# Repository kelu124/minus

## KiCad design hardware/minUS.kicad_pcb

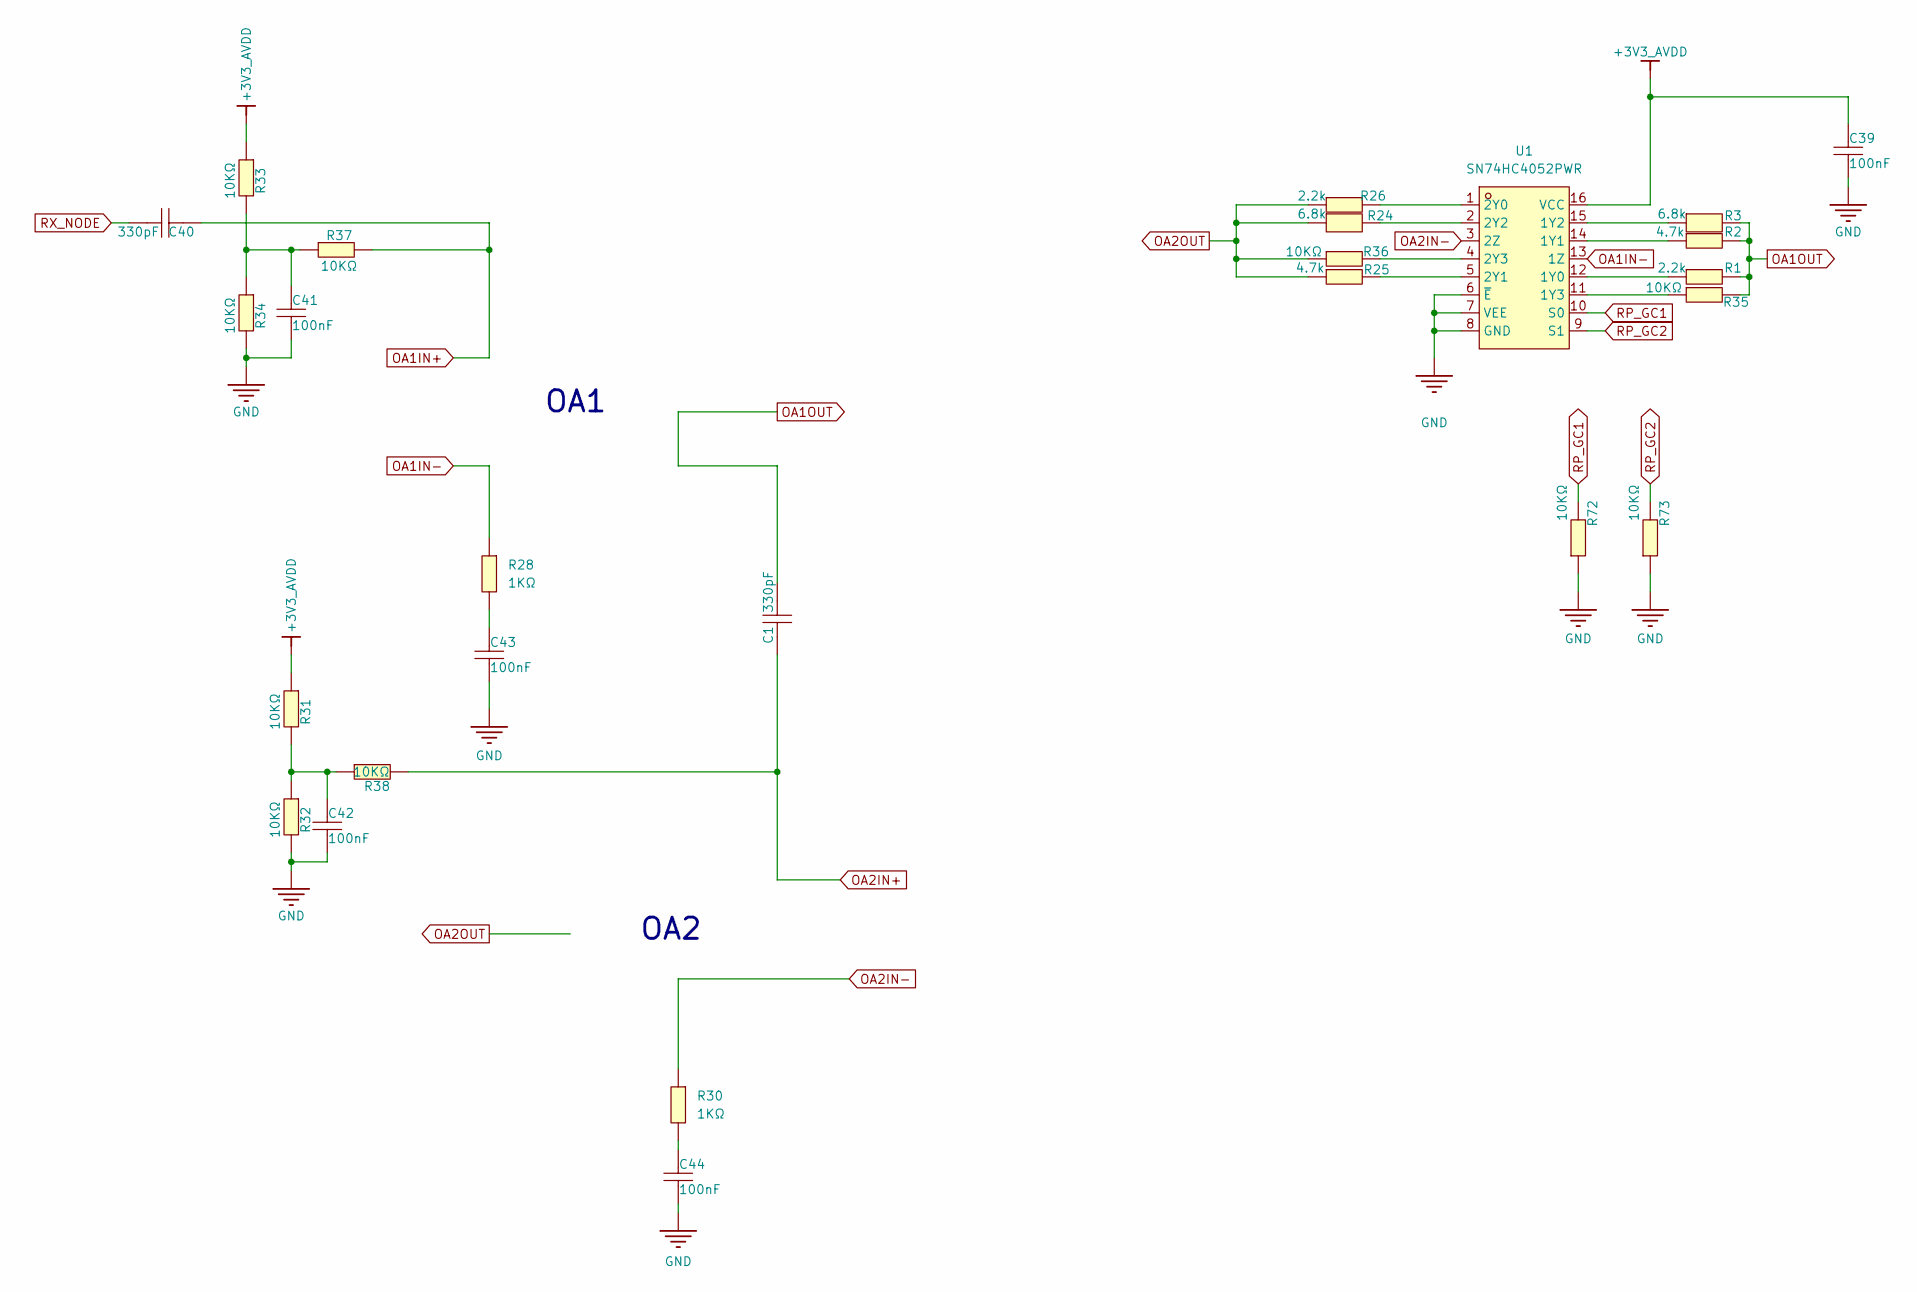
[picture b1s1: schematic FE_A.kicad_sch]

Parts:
C1, C40: CSA0402C0G331J500GT; C0402; MPN CSA0402C0G331J500GT; LCSC Part C48642894
C39, C41, C42, C43, C44: 100nF; C0402; MPN CC0402KRX7R9BB104; LCSC Part C152814
R1, R26: RC0402FR-072K2L; R0402; MPN RC0402FR-072K2L; LCSC Part C114762
R2, R25: RC0402FR-074K7L; R0402; MPN RC0402FR-074K7L; LCSC Part C105871
R3, R24: FRC0402F6801TS; R0402; MPN FRC0402F6801TS; LCSC Part C2906876
R28, R30: 1KΩ; R0402; MPN 0402WGF1001TCE; LCSC Part C11702
R31, R32, R33, R34, R35, R36, R37, R38, R72, R73: 10KΩ; R0402; MPN 0402WGF1002TCE; LCSC Part C25744
U1: SN74HC4052PWR; TSSOP-16_L5.0-W4.3-P0.65-LS6.4-BL; MPN SN74HC4052PWR(LX); LCSC Part C22449643

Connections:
+3V3_AVDD: C39.2, R31.1, R33.1, U1.16 (VCC); also elsewhere on the board
GND: C39.1, C41.1, C42.1, C43.1, C44.1, R32.2, R34.2, R72.1, R73.1, U1.6 (~E), U1.7 (VEE), U1.8 (GND); also elsewhere on the board
unnamed: C41.2, R33.2, R34.1, R37.1
unnamed: C42.2, R31.2, R32.1, R38.1
unnamed: C43.2, R28.2
unnamed: C44.2, R30.2
unnamed: R1.1, U1.12 (1Y0)
unnamed: R2.1, U1.14 (1Y1)
unnamed: R3.1, U1.15 (1Y2)
unnamed: R35.1, U1.11 (1Y3)
unnamed: R26.2, U1.1 (2Y0)
unnamed: R25.2, U1.5 (2Y1)
unnamed: R24.2, U1.2 (2Y2)
unnamed: R36.2, U1.4 (2Y3)
OA1IN+: C40.1, R37.2; also elsewhere on the board
OA1IN-: R28.1, U1.13 (1Z); also elsewhere on the board
OA1OUT: C1.2, R1.2, R2.2, R3.2, R35.2; also elsewhere on the board
OA2IN+: C1.1, R38.2; also elsewhere on the board
OA2IN-: R30.1, U1.3 (2Z); also elsewhere on the board
OA2OUT: R24.1, R25.1, R26.1, R36.1; also elsewhere on the board
RP_GC1: R72.2, U1.10 (S0); also elsewhere on the board
RP_GC2: R73.2, U1.9 (S1); also elsewhere on the board
RX_NODE: C40.2; also elsewhere on the board

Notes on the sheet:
OA1
OA2

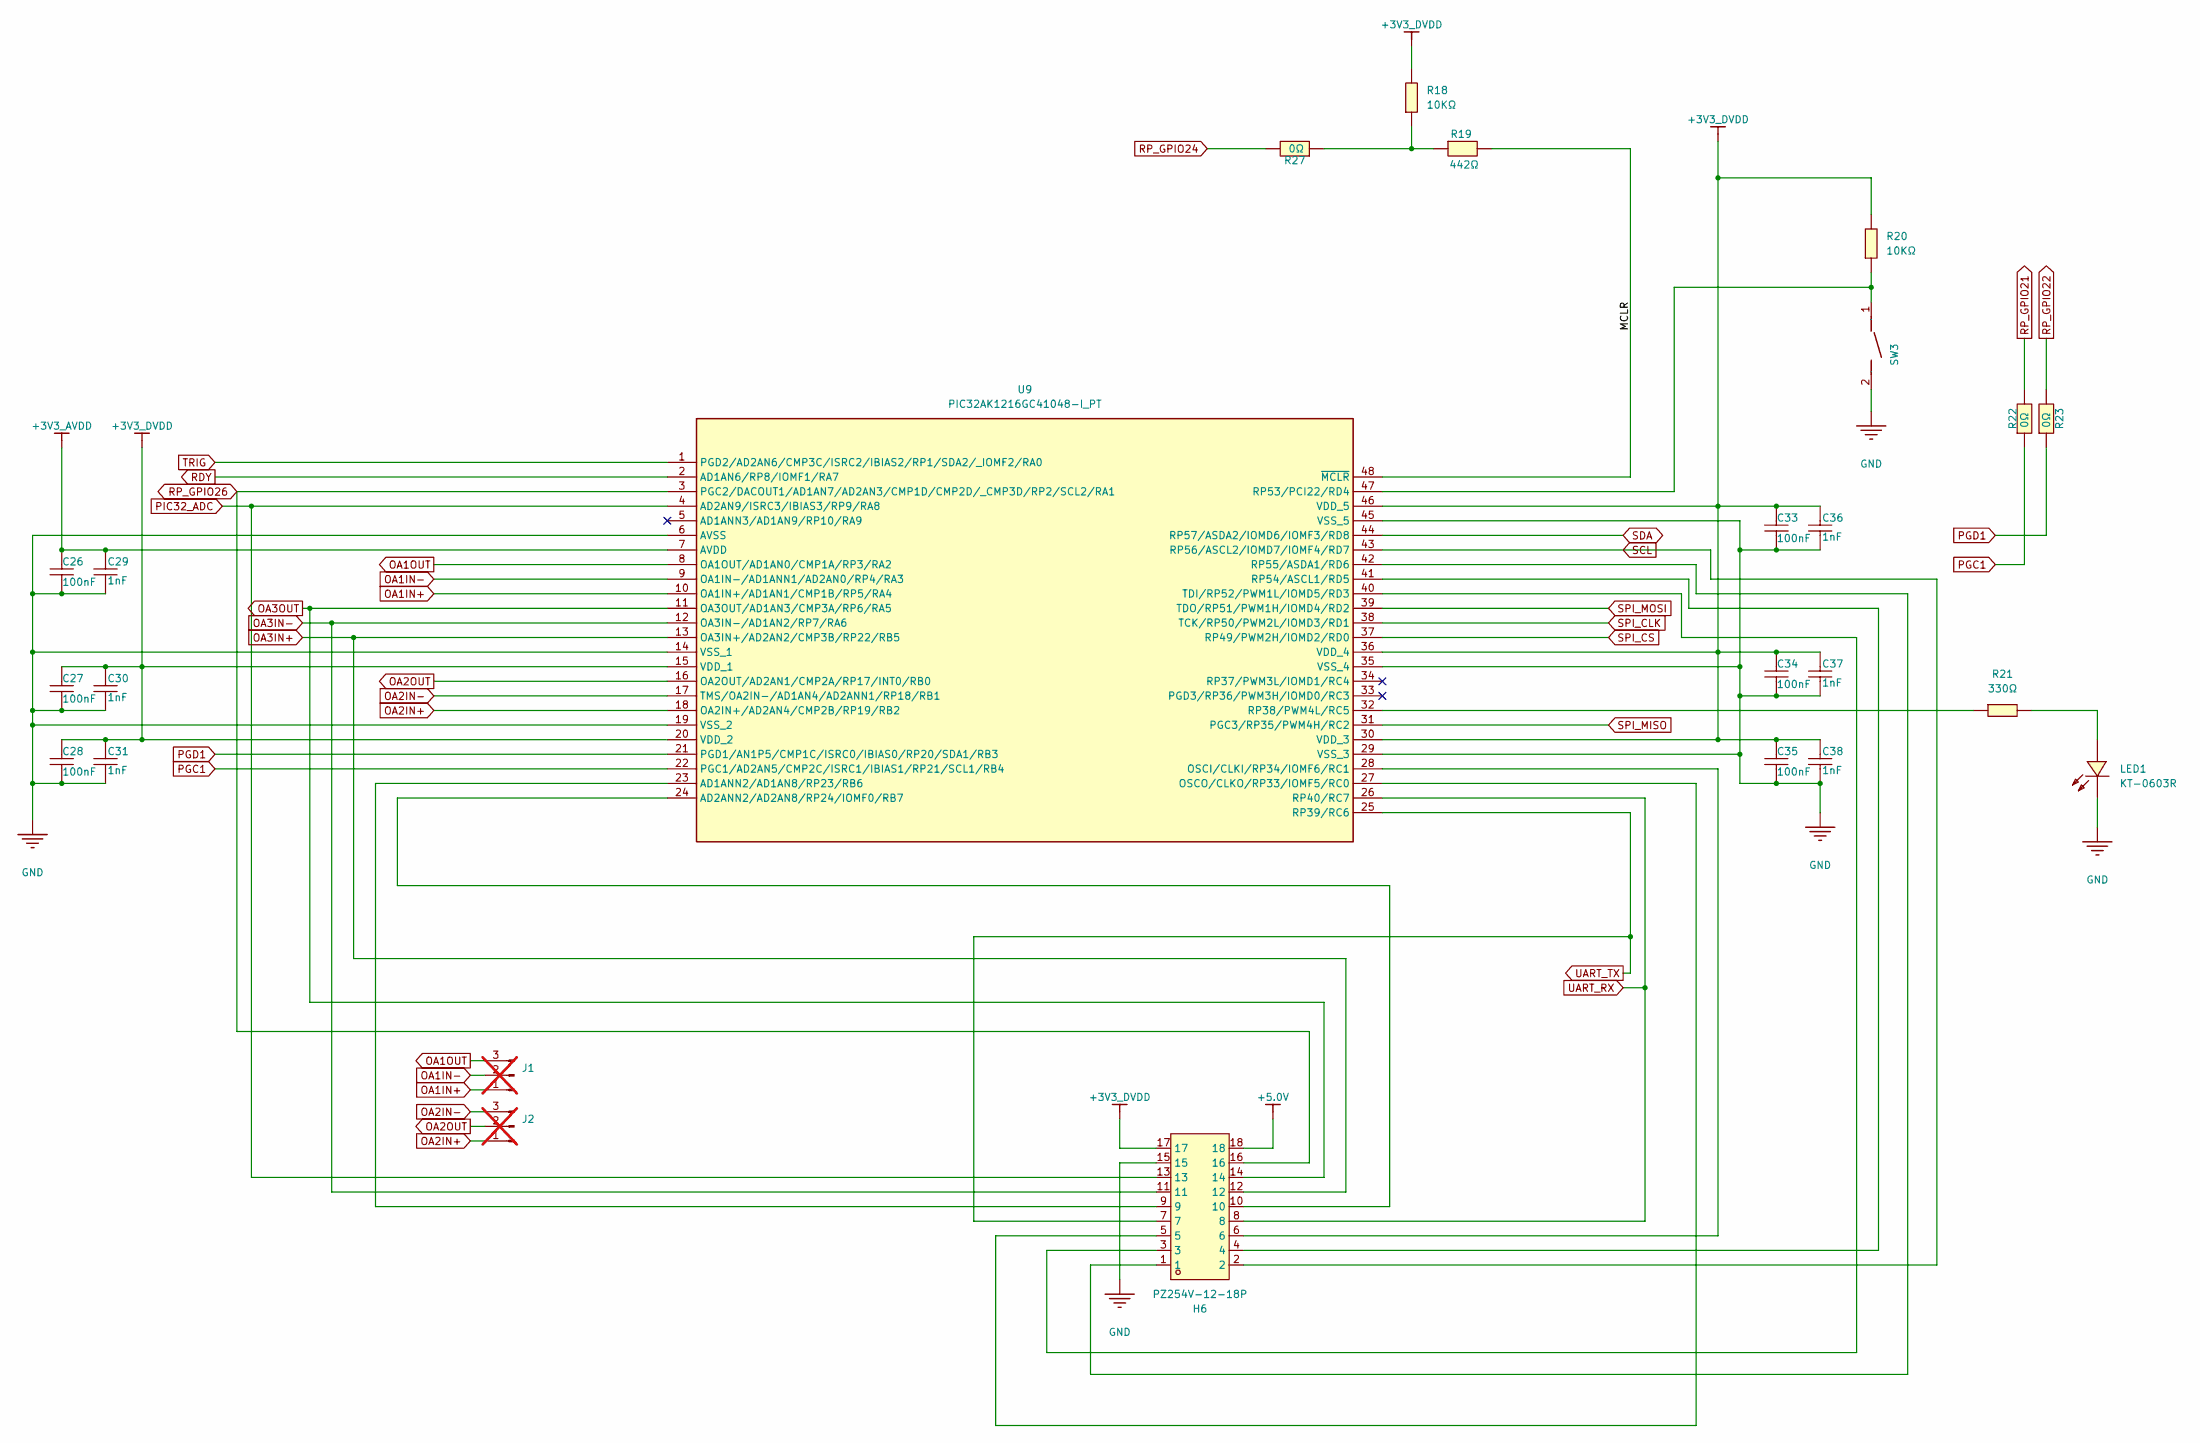
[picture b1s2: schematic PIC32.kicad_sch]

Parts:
C26, C27, C28, C33, C34, C35: 100nF; C0402; MPN CC0402KRX7R9BB104; LCSC Part C152814
C29, C30, C31, C36, C37, C38: 1nF; C0402; MPN CL05B102KB5NNNC; LCSC Part C14442
H6: PZ254V-12-18P; HDR-TH_18P-P2.54-V-M-R2-C9-S2.54; MPN PZ254V-12-18P; LCSC Part C492426
J1, J2: Conn_01x03_Pin; PinSocket_1x03_P2.54mm_Vertical; LCSC Part C49257; not fitted
LED1: KT-0603R; LED-SMD_L1.6-W0.8-R-RD; MPN KT-0603R; LCSC Part C2286
R18, R20: 10KΩ; R0402; MPN 0402WGF1002TCE; LCSC Part C25744
R19: 442Ω; R0402; MPN RC-02K4420FT; LCSC Part C453691
R21: 330Ω; R0402; MPN RC0402FR-07330RL; LCSC Part C105875
R22, R23, R27: 0Ω; R0402; MPN RCS04020000Z0ED; LCSC Part C844673
SW3: TS-1088-AR02016; SW-SMD_L3.9-W3.0-P4.45; Manufacturer Part TS-1088-AR02016; LCSC Part C720477
U9: PIC32AK1216GC41048-I_PT; QFP50P900X900X120-48N; Mouser Part Number 579-K1216GC41048IPT

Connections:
+3V3_AVDD: C26.2, C29.2, U9.7 (AVDD); also elsewhere on the board
+3V3_DVDD: C27.2, C28.2, C30.2, C31.2, C33.2, C34.2, C35.2, C36.2, C37.2, C38.2, H6.17, R18.2, R20.2, U9.15 (VDD_1), U9.20 (VDD_2), U9.30 (VDD_3), U9.36 (VDD_4), U9.46 (VDD_5); also elsewhere on the board
+5.0V: H6.18; also elsewhere on the board
/PIC32/MCLR: R19.2, U9.48 (~MCLR)
GND: C26.1, C27.1, C28.1, C29.1, C30.1, C31.1, C33.1, C34.1, C35.1, C36.1, C37.1, C38.1, H6.15, LED1.2 (K), SW3.2, U9.6 (AVSS), U9.14 (VSS_1), U9.19 (VSS_2), U9.29 (VSS_3), U9.35 (VSS_4), U9.45 (VSS_5); also elsewhere on the board
unnamed: LED1.1 (A), R21.2
unnamed: R18.1, R19.1, R27.1
unnamed: H6.9, U9.23 (AD1ANN2/AD1AN8/RP23/RB6)
unnamed: H6.10, U9.24 (AD2ANN2/AD2AN8/RP24/IOMF0/RB7)
unnamed: H6.6, U9.28 (OSCI/CLKI/RP34/IOMF6/RC1)
unnamed: H6.5, U9.27 (OSCO/CLKO/RP33/IOMF5/RC0)
unnamed: R21.1, U9.32 (RP38/PWM4L/RC5)
unnamed: R20.1, SW3.1, U9.47 (RP53/PCI22/RD4)
unnamed: H6.4, U9.41 (RP54/ASCL1/RD5)
unnamed: H6.1, U9.42 (RP55/ASDA1/RD6)
unnamed: H6.3, U9.40 (TDI/RP52/PWM1L/IOMD5/RD3)
OA1IN+: J1.1, U9.10 (OA1IN+/AD1AN1/CMP1B/RP5/RA4); also elsewhere on the board
OA1IN-: J1.2, U9.9 (OA1IN-/AD1ANN1/AD2AN0/RP4/RA3); also elsewhere on the board
OA1OUT: J1.3, U9.8 (OA1OUT/AD1AN0/CMP1A/RP3/RA2); also elsewhere on the board
OA2IN+: J2.1, U9.18 (OA2IN+/AD2AN4/CMP2B/RP19/RB2); also elsewhere on the board
OA2IN-: J2.3, U9.17 (TMS/OA2IN-/AD1AN4/AD2ANN1/RP18/RB1); also elsewhere on the board
OA2OUT: J2.2, U9.16 (OA2OUT/AD2AN1/CMP2A/RP17/INT0/RB0); also elsewhere on the board
OA3IN+: H6.12, U9.13 (OA3IN+/AD2AN2/CMP3B/RP22/RB5)
OA3IN-: H6.11, U9.12 (OA3IN-/AD1AN2/RP7/RA6)
OA3OUT: H6.14, U9.11 (OA3OUT/AD1AN3/CMP3A/RP6/RA5)
PGC1: R22.1, U9.22 (PGC1/AD2AN5/CMP2C/ISRC1/IBIAS1/RP21/SCL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)
PGD1: R23.1, U9.21 (PGD1/AN1P5/CMP1C/ISRC0/IBIAS0/RP20/SDA1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)
PIC32_ADC: H6.13, U9.4 (AD2AN9/ISRC3/IBIAS3/RP9/RA8); also elsewhere on the board
RDY: U9.2 (AD1AN6/RP8/IOMF1/RA7); also elsewhere on the board
RP_GPIO21: R22.2; also elsewhere on the board
RP_GPIO22: R23.2; also elsewhere on the board
RP_GPIO24: R27.2; also elsewhere on the board
RP_GPIO26: H6.16, U9.3 (PGC2/DACOUT1/AD1AN7/AD2AN3/CMP1D/CMP2D/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); also elsewhere on the board
SCL: H6.2, U9.43 (RP56/ASCL2/IOMD7/IOMF4/RD7); also elsewhere on the board
SDA: U9.44 (RP57/ASDA2/IOMD6/IOMF3/RD8); also elsewhere on the board
SPI_CLK: U9.38 (TCK/RP50/PWM2L/IOMD3/RD1); also elsewhere on the board
SPI_CS: U9.37 (RP49/PWM2H/IOMD2/RD0); also elsewhere on the board
SPI_MISO: U9.31 (PGC3/RP35/PWM4H/RC2); also elsewhere on the board
SPI_MOSI: U9.39 (TDO/RP51/PWM1H/IOMD4/RD2); also elsewhere on the board
TRIG: U9.1 (PGD2/AD2AN6/CMP3C/ISRC2/IBIAS2/RP1/SDA2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); also elsewhere on the board
UART_RX: H6.8, U9.26 (RP40/RC7); also elsewhere on the board
UART_TX: H6.7, U9.25 (RP39/RC6); also elsewhere on the board

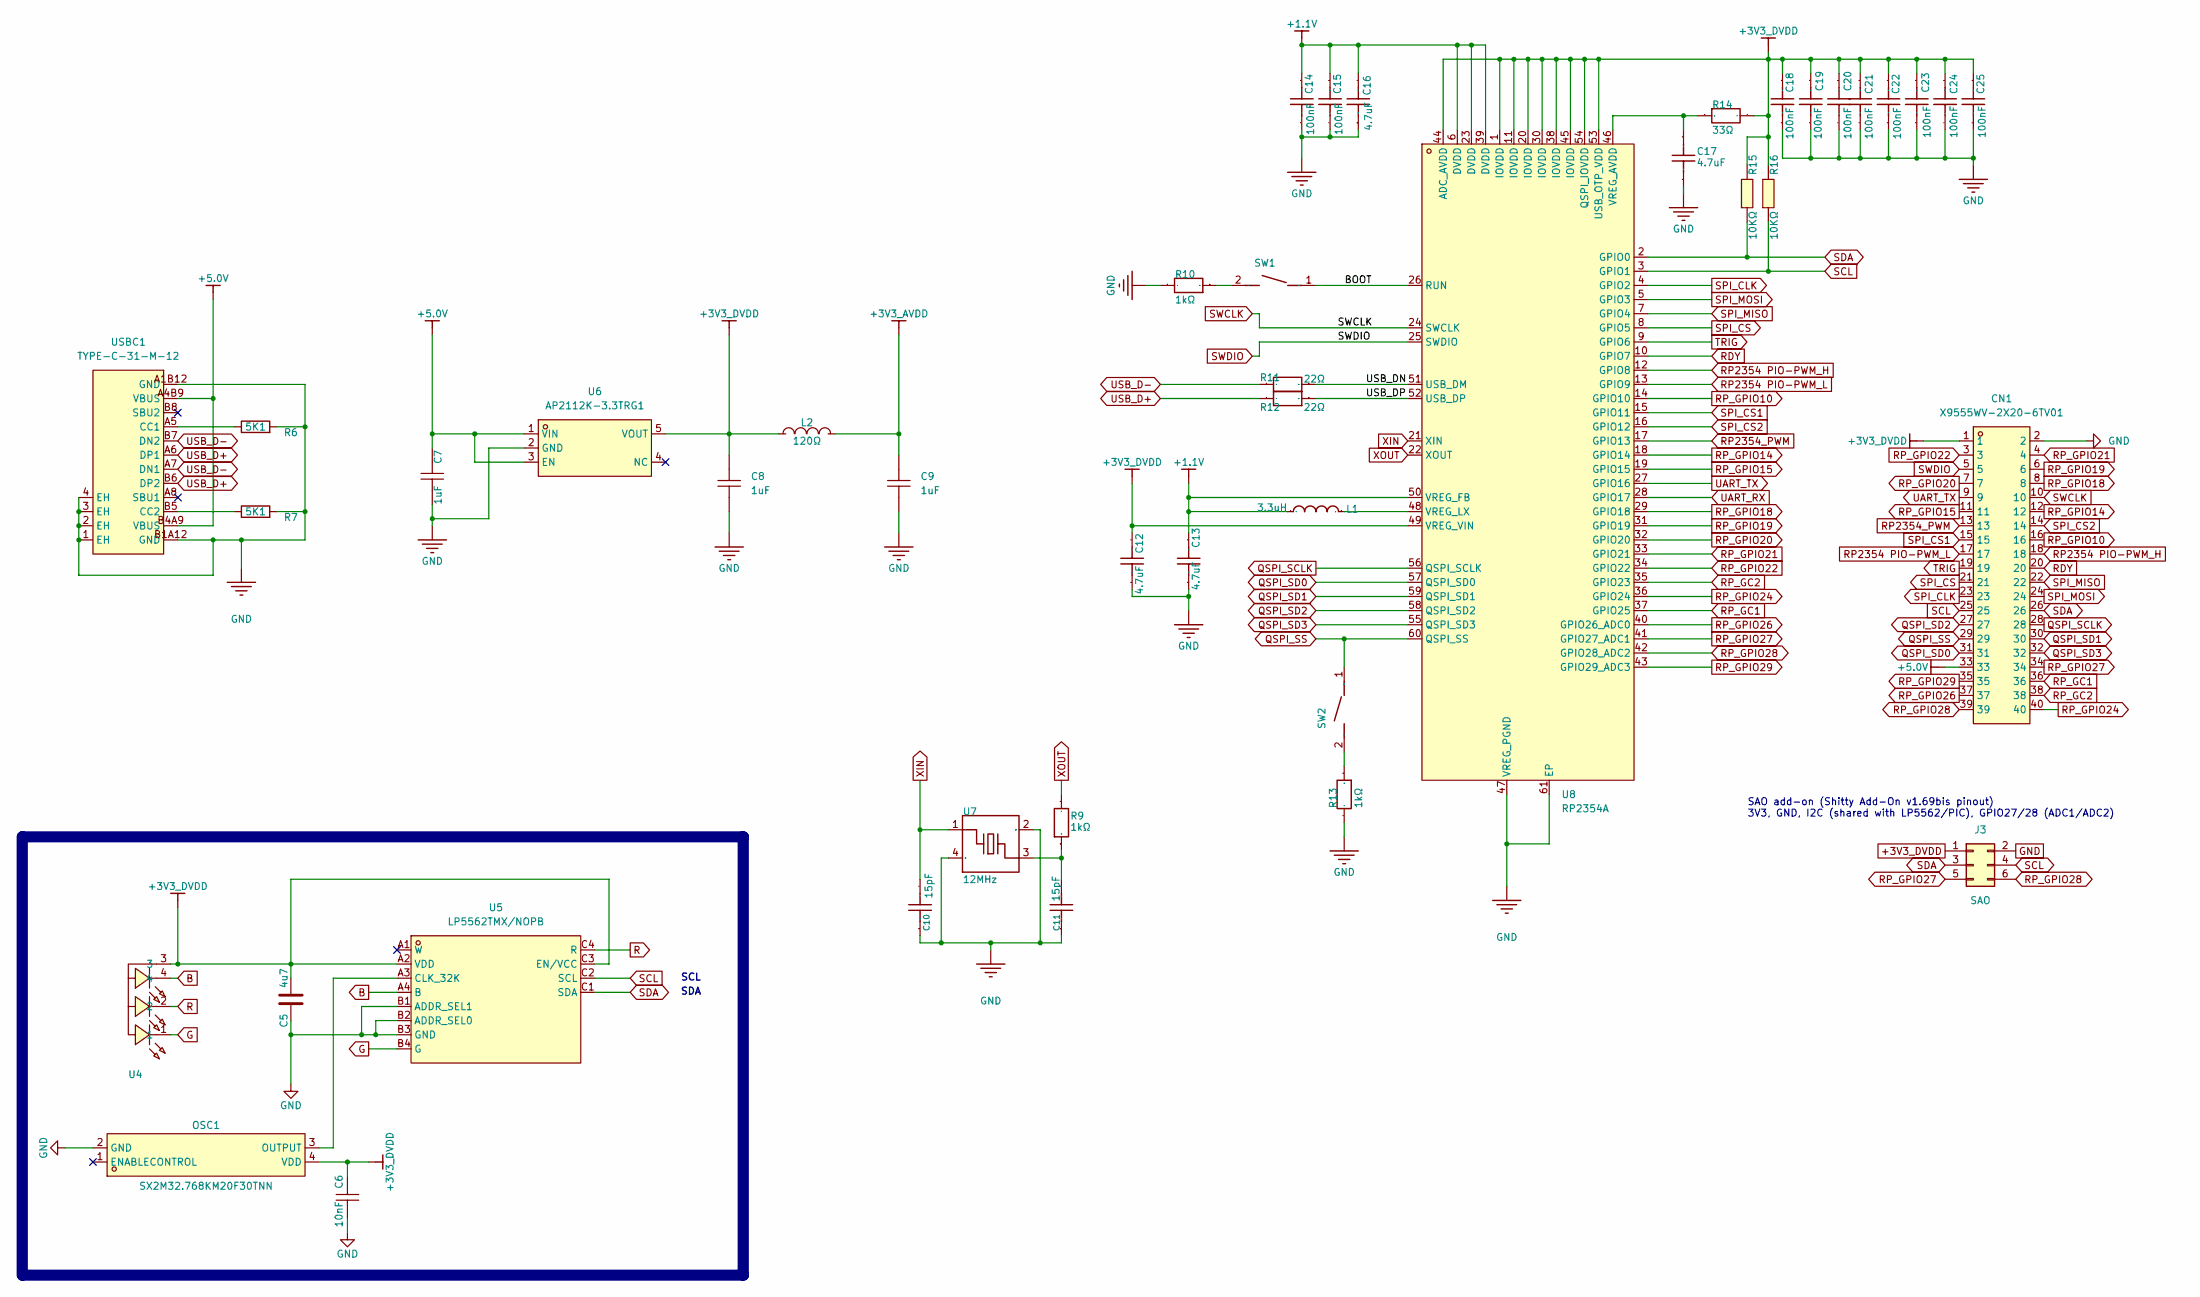
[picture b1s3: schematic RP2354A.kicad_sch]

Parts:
C5: 4u7; C_0402_1005Metric; MPN CC0402KRX5R6BB475; LCSC Part C326586
C6: 10nF; C0402; MPN CL05B103KB5NNNC; LCSC Part C15195
C7, C8, C9: 1uF; C0402; MPN CL05A105KA5NQNC; LCSC Part C52923
C10, C11: 15pF; C0402; Manufacturer Part CC0402FRNPO9BN150; LCSC Part C326803
C12, C13, C16, C17: 4.7uF; C0402; Manufacturer Part GRM155C61E475ME15D; LCSC Part C5718966
C14, C15, C18, C19, C20, C21, C22, C23, C24, C25: 100nF; C0402; Manufacturer Part 0402B104K500CT; LCSC Part C152814
CN1: X9555WV-2X20-6TV01; IDC-TH_40P-P2.54_X9555WV-2X20-6TV01; MPN X9555WV-2x20-6TV01; LCSC Part C2884558
J3: SAO; PinHeader_2x03_P2.54mm_Vertical; MPN PZ254V-12-6P; LCSC Part C492420
L1: 3.3uH; IND-SMD_L2.0-W1.6_AOTA-B201610S3R3-101-T; Manufacturer Part AOTA-B201610S3R3-101-T; LCSC Part C42411119
L2: CBW321609U121T; L1206; MPN CBW321609U121T; LCSC Part C139197
OSC1: SX2M32.768KM20F30TNN; OSC-SMD_4P-L2.5-W2.0-BL; MPN SX2M32.768KM20F30TNN; LCSC Part C2901603
R6, R7: 5K1; R_0402_1005Metric; MPN RC0402JR-075K1L; LCSC Part C105873
R9, R10, R13: 1kΩ; R0402; Manufacturer Part FRC0402F1001TS; LCSC Part C2906864
R11, R12: 22Ω; R0402; Manufacturer Part FRC0402F22R0TS; LCSC Part C2929994
R14: 33Ω; R0402; Manufacturer Part FRC0402J330 TS; LCSC Part C2906931
R15, R16: 10KΩ; R0402; MPN 0402WGF1002TCE; LCSC Part C25744
SW1, SW2: TS-1088-AR02016; SW-SMD_L3.9-W3.0-P4.45; Manufacturer Part TS-1088-AR02016; LCSC Part C720477
U4: A-SP1943B1GHR6C-C01-2T; LED-SMD_4P-L1.6-W1.5-BL_A-SP1943B1GHR6C-C01-2T; MPN A-SP1943B1GHR6C-C01-2T; LCSC Part C19171342
U5: LP5562TMX/NOPB; DSBGA-12_L1.7-W1.3-R3-C4-P0.40-TL; MPN LP5562TMX/NOPB; LCSC Part C544465
U6: AP2112K-3.3TRG1; SOT-25-5_L2.9-W1.6-P0.95-LS2.8-BL; MPN AP2112K-3.3TRG1; LCSC Part C51118
U7: 12MHz; OSC-SMD_4P-L3.2-W2.5-BL_SIT8008BI; Manufacturer Part ABM8-272-T3; LCSC Part C20625731
U8: RP2354A; QFN-60_L7.0-W7.0-P0.40-TL-EP3.4; MPN RP2354A; LCSC Part C41378174
USBC1: TYPE-C-31-M-12; USB-C_SMD-TYPE-C-31-M-12_1; MPN TYPE-C-31-M-12; LCSC Part C165948

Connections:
+1.1V: C13.2, C14.1, C15.1, C16.2, L1.2, U8.6 (DVDD), U8.23 (DVDD), U8.39 (DVDD), U8.50 (VREG_FB)
+3V3_AVDD: C9.2, L2.2; also elsewhere on the board
+3V3_DVDD: C5.2, C6.2, C8.2, C12.2, C18.1, C19.1, C20.1, C21.1, C22.1, C23.1, C24.1, C25.1, CN1.1, J3.1, L2.1, OSC1.4 (VDD), R14.2, R15.2, R16.2, U4.3, U5.A2 (VDD), U5.C3 (EN/VCC), U6.5 (VOUT), U8.1 (IOVDD), U8.11 (IOVDD), U8.20 (IOVDD), U8.30 (IOVDD), U8.38 (IOVDD), U8.44 (ADC_AVDD), U8.45 (IOVDD), U8.49 (VREG_VIN), U8.53 (USB_OTP_VDD), U8.54 (QSPI_IOVDD); also elsewhere on the board
+5.0V: C7.2, CN1.33, U6.1 (VIN), U6.3 (EN), USBC1.A4B9 (VBUS), USBC1.B4A9 (VBUS); also elsewhere on the board
/RP2354A/BOOT: SW1.1, U8.26 (RUN)
/RP2354A/USB_DN: R11.1, U8.51 (USB_DM)
/RP2354A/USB_DP: R12.1, U8.52 (USB_DP)
B: U4.4, U5.A4 (B)
G: U4.1, U5.B4 (G)
GND: C5.1, C6.1, C7.1, C8.1, C9.1, C10.1, C11.1, C12.1, C13.1, C14.2, C15.2, C16.1, C17.1, C18.2, C19.2, C20.2, C21.2, C22.2, C23.2, C24.2, C25.2, CN1.2, J3.2, OSC1.2 (GND), R6.2, R7.2, R10.2, R13.2, U5.B1 (ADDR_SEL1), U5.B2 (ADDR_SEL0), U5.B3 (GND), U6.2 (GND), U7.2 (GND), U7.4 (GND), U8.47 (VREG_PGND), U8.61 (EP), USBC1.1 (EH), USBC1.2 (EH), USBC1.3 (EH), USBC1.4 (EH), USBC1.A1B12 (GND), USBC1.B1A12 (GND); also elsewhere on the board
unnamed: C11.2, R9.1, U7.3
unnamed: OSC1.3 (OUTPUT), U5.A3 (CLK_32K)
unnamed: R10.1, SW1.2
unnamed: R13.1, SW2.2
unnamed: C17.2, R14.1, U8.46 (VREG_AVDD)
unnamed: L1.1, U8.48 (VREG_LX)
unnamed: R6.1, USBC1.A5 (CC1)
unnamed: R7.1, USBC1.B5 (CC2)
QSPI_SCLK: CN1.28, U8.56 (QSPI_SCLK)
QSPI_SD0: CN1.31, U8.57 (QSPI_SD0)
QSPI_SD1: CN1.30, U8.59 (QSPI_SD1)
QSPI_SD2: CN1.27, U8.58 (QSPI_SD2)
QSPI_SD3: CN1.32, U8.55 (QSPI_SD3)
QSPI_SS: CN1.29, SW2.1, U8.60 (QSPI_SS)
R: U4.2, U5.C4 (R)
RDY: CN1.20, U8.10 (GPIO7); also elsewhere on the board
RP2354 PIO-PWM_H: CN1.18, U8.12 (GPIO8); also elsewhere on the board
RP2354 PIO-PWM_L: CN1.17, U8.13 (GPIO9); also elsewhere on the board
RP2354_PWM: CN1.13, U8.17 (GPIO13)
RP_GC1: CN1.36, U8.37 (GPIO25); also elsewhere on the board
RP_GC2: CN1.38, U8.35 (GPIO23); also elsewhere on the board
RP_GPIO10: CN1.16, U8.14 (GPIO10)
RP_GPIO14: CN1.12, U8.18 (GPIO14)
RP_GPIO15: CN1.11, U8.19 (GPIO15)
RP_GPIO18: CN1.8, U8.29 (GPIO18)
RP_GPIO19: CN1.6, U8.31 (GPIO19)
RP_GPIO20: CN1.7, U8.32 (GPIO20)
RP_GPIO21: CN1.4, U8.33 (GPIO21); also elsewhere on the board
RP_GPIO22: CN1.3, U8.34 (GPIO22); also elsewhere on the board
RP_GPIO24: CN1.40, U8.36 (GPIO24); also elsewhere on the board
RP_GPIO26: CN1.37, U8.40 (GPIO26_ADC0); also elsewhere on the board
RP_GPIO27: CN1.34, J3.5, U8.41 (GPIO27_ADC1)
RP_GPIO28: CN1.39, J3.6, U8.42 (GPIO28_ADC2)
RP_GPIO29: CN1.35, U8.43 (GPIO29_ADC3)
SCL: CN1.25, J3.4, R16.1, U5.C2 (SCL), U8.3 (GPIO1); also elsewhere on the board
SDA: CN1.26, J3.3, R15.1, U5.C1 (SDA), U8.2 (GPIO0); also elsewhere on the board
SPI_CLK: CN1.23, U8.4 (GPIO2); also elsewhere on the board
SPI_CS: CN1.21, U8.8 (GPIO5); also elsewhere on the board
SPI_CS1: CN1.15, U8.15 (GPIO11)
SPI_CS2: CN1.14, U8.16 (GPIO12)
SPI_MISO: CN1.22, U8.7 (GPIO4); also elsewhere on the board
SPI_MOSI: CN1.24, U8.5 (GPIO3); also elsewhere on the board
SWCLK: CN1.10, U8.24 (SWCLK)
SWDIO: CN1.5, U8.25 (SWDIO)
TRIG: CN1.19, U8.9 (GPIO6); also elsewhere on the board
UART_RX: U8.28 (GPIO17); also elsewhere on the board
UART_TX: CN1.9, U8.27 (GPIO16); also elsewhere on the board
USB_D+: R12.2, USBC1.A6 (DP1), USBC1.B6 (DP2)
USB_D-: R11.2, USBC1.A7 (DN1), USBC1.B7 (DN2)
XIN: C10.2, U7.1, U8.21 (XIN)
XOUT: R9.2, U8.22 (XOUT)

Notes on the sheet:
SDA
SCL
SAO add-on (Shitty Add-On v1.69bis pinout) 3V3, GND, I2C (shared with LP5562/PIC), GPIO27/28 (ADC1/ADC2)

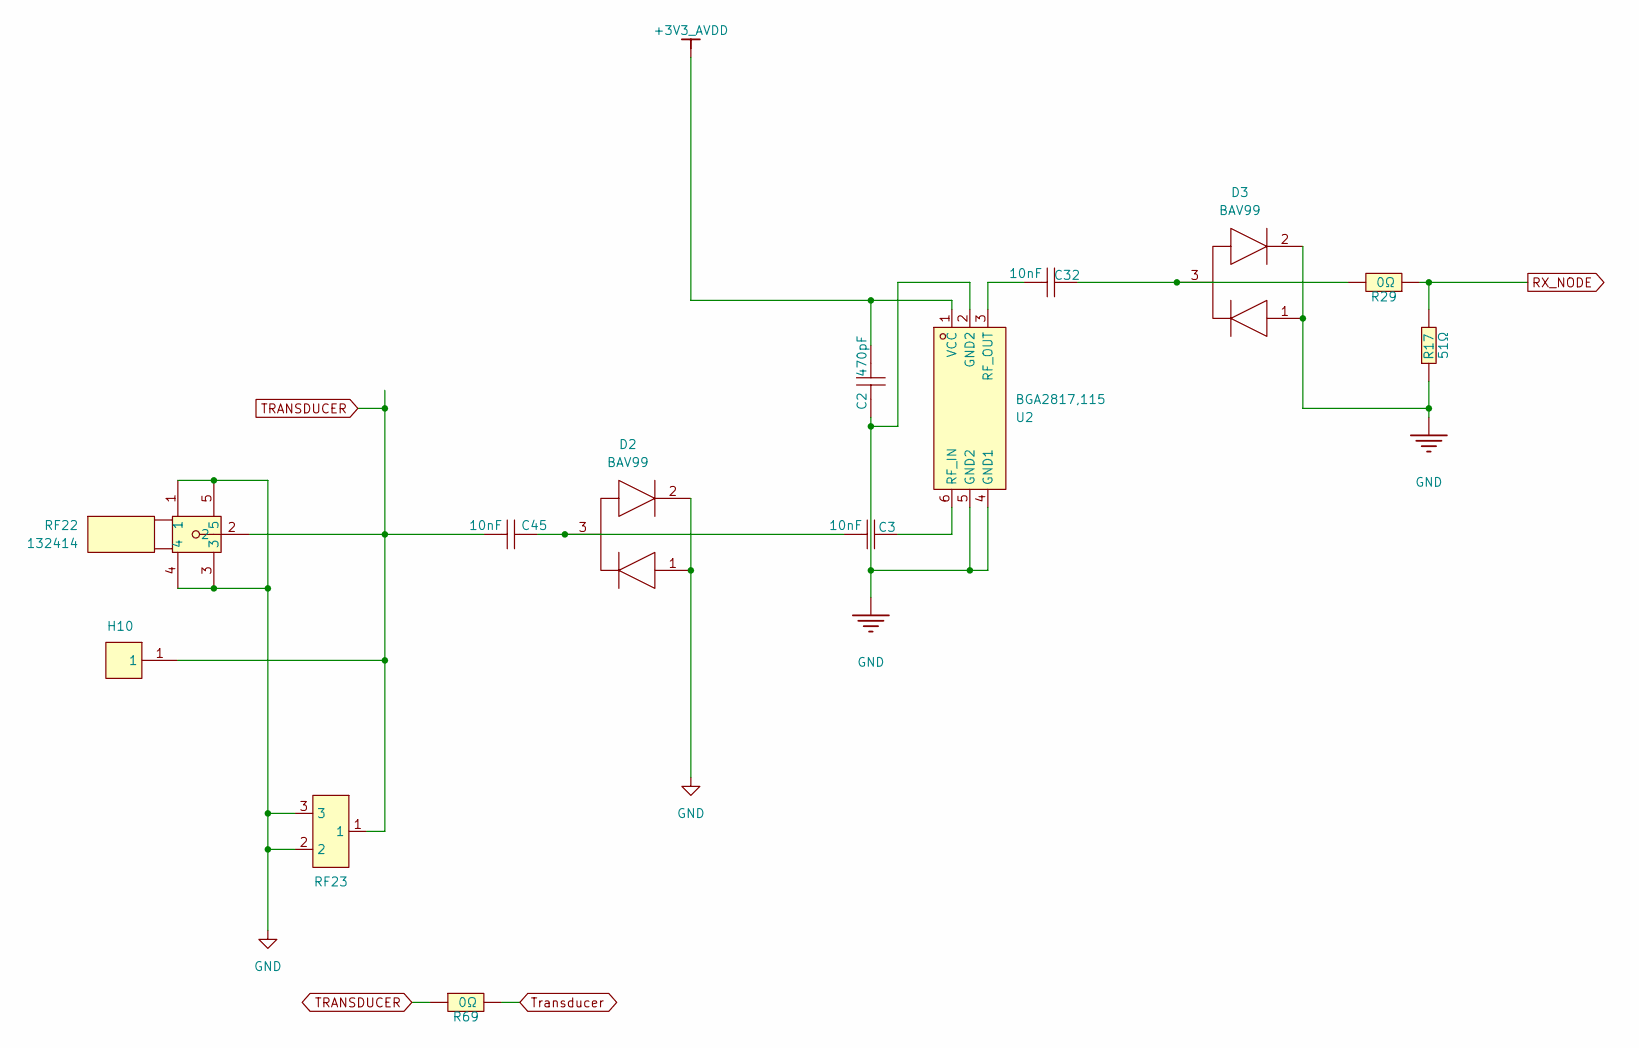
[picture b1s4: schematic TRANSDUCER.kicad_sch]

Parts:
C2: CC0402KRX7R9BB471; C0402; MPN CC0402KRX7R9BB471; LCSC Part C106207
C3, C32, C45: CL05B103KB5NNNC; C0402; MPN CL05B103KB5NNNC; LCSC Part C15195
D2, D3: BAV99; SOT-23; Mouser Part Number 621-BAV99-F
H10: PZ254V-11-01P; HDR-TH_1P-P2.54-V-M; MPN PZ254V-11-01P; LCSC Part C492400
R17: 0402WGF510JTCE; R0402; MPN 0402WGF510JTCE; LCSC Part C25125
R29, R69: 0Ω; R0402; MPN RCS04020000Z0ED; LCSC Part C844673
RF22: 132414; SMA-SMD_132414; MPN 132414; LCSC Part C6363889
RF23: CONUFL001-SMD-T; IPEX-SMD_3P-L2.6-W2.6-LS3.0; MPN CONUFL001-SMD-T; LCSC Part C22418213
U2: BGA2817,115; SC-70-6_L2.0-W1.3-P0.65-LS2.1-BR; MPN BGA2817,115; LCSC Part C2654187

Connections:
+3V3_AVDD: C2.2, U2.1 (VCC); also elsewhere on the board
GND: C2.1, D2.1, D2.2, D3.1, D3.2, R17.1, RF22.1, RF22.3, RF22.4, RF22.5, RF23.2, RF23.3, U2.2 (GND2), U2.4 (GND1), U2.5 (GND2); also elsewhere on the board
unnamed: C3.1, C45.2, D2.3
unnamed: C32.2, D3.3, R29.2
unnamed: C3.2, U2.6 (RF_IN)
unnamed: C32.1, U2.3 (RF_OUT)
RX_NODE: R17.2, R29.1; also elsewhere on the board
TRANSDUCER: C45.1, H10.1 (1_1), R69.1, RF22.2, RF23.1
Transducer: R69.2; also elsewhere on the board

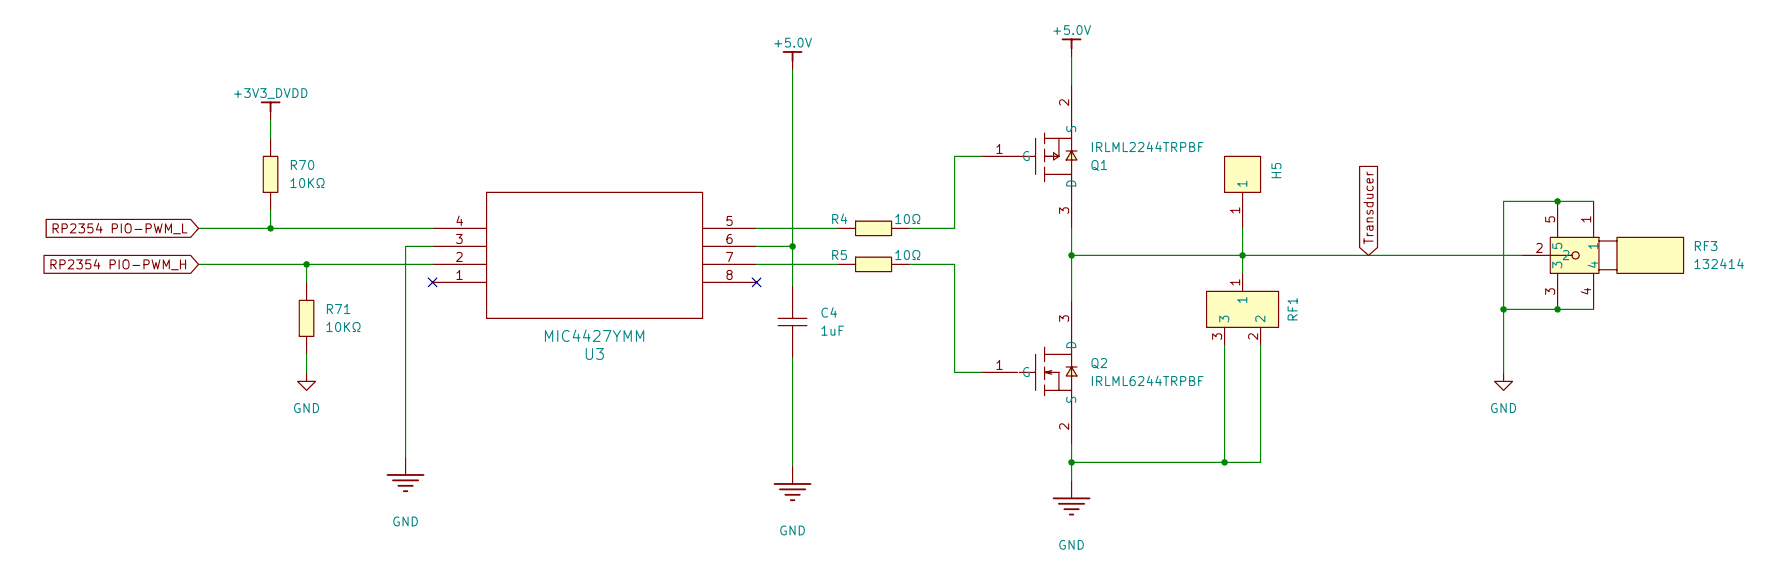
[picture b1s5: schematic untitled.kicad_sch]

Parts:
C4: 1uF; C0402; MPN CL05A105KA5NQNC; LCSC Part C52923
H5: PZ254V-11-01P; HDR-TH_1P-P2.54-V-M; MPN PZ254V-11-01P; LCSC Part C492400
Q1: IRLML2244TRPBF; SOT-23-3_L2.9-W1.6-P1.90-LS2.8-BR; MPN IRLML2244TRPBF; LCSC Part C169763
Q2: IRLML6244TRPBF; SOT-23-3_L2.9-W1.3-P1.90-LS2.4-BR; MPN IRLML6244TRPBF; LCSC Part C143946
R4, R5: 10Ω; R0402; MPN RC0402FR-0710RL; LCSC Part C138066
R70, R71: 10KΩ; R0402; MPN 0402WGF1002TCE; LCSC Part C25744
RF1: CONUFL001-SMD-T; IPEX-SMD_3P-L2.6-W2.6-LS3.0; MPN CONUFL001-SMD-T; LCSC Part C22418213
RF3: 132414; SMA-SMD_132414; MPN 132414; LCSC Part C6363889
U3: MIC4427YMM; MSOP8_MC_MCH-M; LCSC Part C152165

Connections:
+3V3_DVDD: R70.2; also elsewhere on the board
+5.0V: C4.2, Q1.2 (S), U3.6; also elsewhere on the board
GND: C4.1, Q2.2 (S), R71.1, RF1.2, RF1.3, RF3.1, RF3.3, RF3.4, RF3.5, U3.3; also elsewhere on the board
unnamed: Q1.1 (G), R4.2
unnamed: Q2.1 (G), R5.2
unnamed: R4.1, U3.5
unnamed: R5.1, U3.7
RP2354 PIO-PWM_H: R71.2, U3.2; also elsewhere on the board
RP2354 PIO-PWM_L: R70.1, U3.4; also elsewhere on the board
Transducer: H5.1 (1_1), Q1.3 (D), Q2.3 (D), RF1.1, RF3.2; also elsewhere on the board

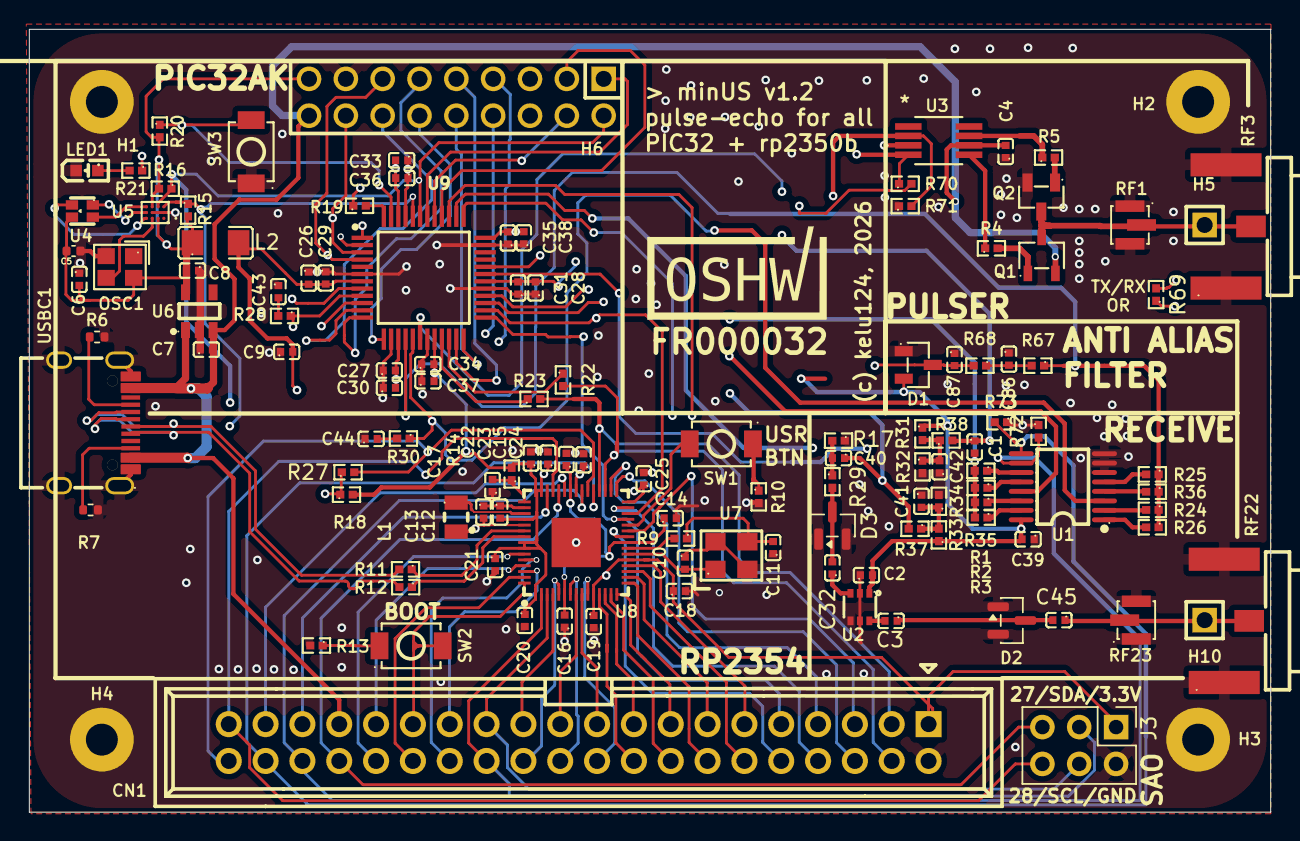
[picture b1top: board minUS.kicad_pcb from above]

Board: 4 copper layers, 85.6 x 54.0 mm, 126 parts (0 on the bottom side), 109 nets.

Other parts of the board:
C86, C87: 56pF; C0402
D1: BAT54S_C916425; SOT-23-3_L2.9-W1.3-P1.90-LS2.4-BR
H1, H2, H3, H4: MountingHole_Pad; MountingHole_2.2mm_M2_Pad
R67, R68: 100Ω; R0402

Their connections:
+3V3_AVDD: D1.2 (K); also elsewhere on the board
GND: C86.1, C87.1, D1.1 (A), H1.1 (1_1), H2.1 (1_1), H3.1 (1_1), H4.1 (1_1); also elsewhere on the board
unnamed: C86.2, R67.2, R68.1
OA2OUT: R67.1; also elsewhere on the board
PIC32_ADC: C87.2, D1.3, R68.2; also elsewhere on the board

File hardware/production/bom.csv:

Designator,Footprint,Quantity,Value,LCSC Part #
"C1, C40",C0402,2,CSA0402C0G331J500GT,C48642894
"C10, C11",C0402,2,15pF,C326803
"C12, C13, C16, C17",C0402,4,4.7uF,C5718966
"C14, C15, C18, C19, C20, C21, C22, C23, C24, C25, C26, C27, C28, C33, C34, C35, C39, C41, C42, C43, C44",C0402,21,100nF,C152814
C2,C0402,1,CC0402KRX7R9BB471,C106207
"C29, C30, C31, C36, C37, C38",C0402,6,1nF,C14442
"C3, C32, C45",C0402,3,CL05B103KB5NNNC,C15195
"C4, C7, C8, C9",C0402,4,1uF,C52923
C5,0402,1,4u7,C326586
C6,C0402,1,10nF,C15195
"C86, C87",C0402,2,56pF,C526981
CN1,IDC-TH_40P-P2.54_X9555WV-2X20-6TV01,1,X9555WV-2X20-6TV01,C2884558
D1,SOT-23-3_L2.9-W1.3-P1.90-LS2.4-BR,1,BAT54S_C916425,C916425
"D2, D3",SOT-23,2,BAV99,C2500
"H10, H5",HDR-TH_1P-P2.54-V-M,2,PZ254V-11-01P,C492400
H6,HDR-TH_18P-P2.54-V-M-R2-C9-S2.54,1,PZ254V-12-18P,C492426
J3,PinHeader_2x03_P2.54mm_Vertical,1,SAO,C492420
L1,IND-SMD_L2.0-W1.6_AOTA-B201610S3R3-101-T,1,3.3uH,C42411119
L2,L1206,1,CBW321609U121T,C139197
LED1,LED-SMD_L1.6-W0.8-R-RD,1,KT-0603R,C2286
OSC1,OSC-SMD_4P-L2.5-W2.0-BL,1,SX2M32.768KM20F30TNN,C2901603
Q1,SOT-23-3_L2.9-W1.6-P1.90-LS2.8-BR,1,IRLML2244TRPBF,C169763
Q2,SOT-23-3_L2.9-W1.3-P1.90-LS2.4-BR,1,IRLML6244TRPBF,C143946
"R1, R26",R0402,2,RC0402FR-072K2L,C114762
"R10, R13, R9",R0402,3,1kΩ,C2906864
"R11, R12",R0402,2,22Ω,C2929994
R14,R0402,1,33Ω,C2906931
"R15, R16, R18, R20, R31, R32, R33, R34, R35, R36, R37, R38, R70, R71, R72, R73",R0402,16,10KΩ,C25744
R17,R0402,1,0402WGF510JTCE,C25125
R19,R0402,1,442Ω,C453691
"R2, R25",R0402,2,RC0402FR-074K7L,C105871
R21,R0402,1,330Ω,C105875
"R22, R23, R27, R29, R69",R0402,5,0Ω,C844673
"R24, R3",R0402,2,FRC0402F6801TS,C2906876
"R28, R30",R0402,2,1KΩ,C11702
"R4, R5",R0402,2,10Ω,C138066
"R6, R7",0402,2,5K1,C105873
"R67, R68",R0402,2,100Ω,C25076
"RF1, RF23",IPEX-SMD_3P-L2.6-W2.6-LS3.0,2,CONUFL001-SMD-T,C22418213
"RF22, RF3",SMA-SMD_132414,2,132414,C6363889
"SW1, SW2, SW3",SW-SMD_L3.9-W3.0-P4.45,3,TS-1088-AR02016,C720477
U1,TSSOP-16_L5.0-W4.3-P0.65-LS6.4-BL,1,SN74HC4052PWR,C22449643
U2,SC-70-6_L2.0-W1.3-P0.65-LS2.1-BR,1,"BGA2817,115",C2654187
U3,MSOP8_MC_MCH-M,1,MIC4427YMM,C152165
U4,LED-SMD_4P-L1.6-W1.5-BL_A-SP1943B1GHR6C-C01-2T,1,A-SP1943B1GHR6C-C01-2T,C19171342
U5,DSBGA-12_L1.7-W1.3-R3-C4-P0.40-TL,1,LP5562TMX/NOPB,C544465
U6,SOT-25-5_L2.9-W1.6-P0.95-LS2.8-BL,1,AP2112K-3.3TRG1,C51118
U7,OSC-SMD_4P-L3.2-W2.5-BL_SIT8008BI,1,12MHz,C20625731
U8,QFN-60_L7.0-W7.0-P0.40-TL-EP3.4,1,RP2354A,C41378174
U9,QFP50P900X900X120-48N,1,PIC32AK1216GC41048-I_PT,C46545915
USBC1,USB-C_SMD-TYPE-C-31-M-12_1,1,TYPE-C-31-M-12,C165948
